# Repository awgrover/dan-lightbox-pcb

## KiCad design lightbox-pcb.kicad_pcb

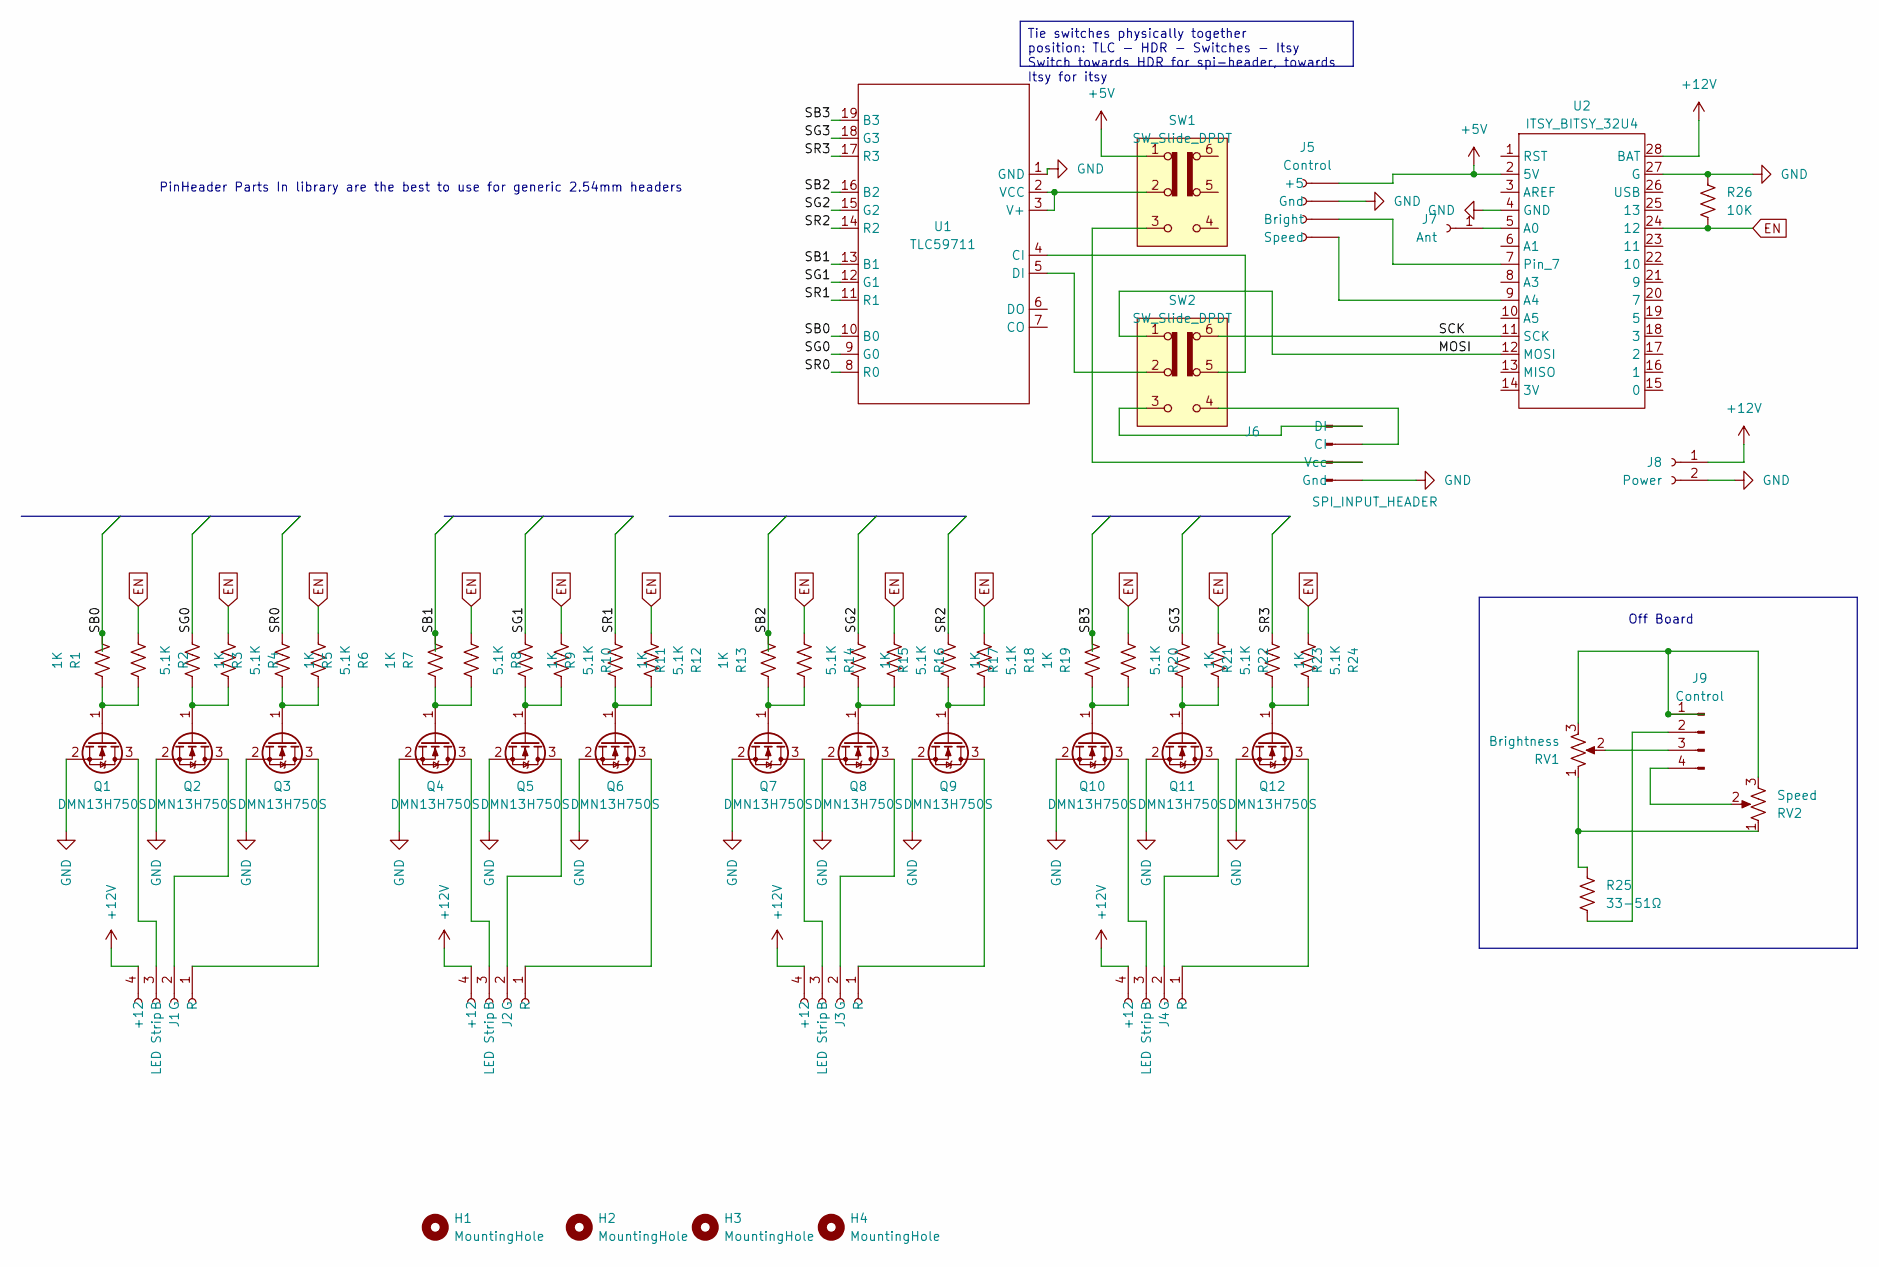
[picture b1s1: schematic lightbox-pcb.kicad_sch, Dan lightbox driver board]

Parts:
H1, H2, H3, H4: MountingHole; MountingHole_4.3mm_M4
J1, J2, J3, J4: LED Strip; PhoenixContact_MC_1,5_4-G-3.5_1x04_P3.50mm_Horizontal
J5: Control; PinHeader_1x04_P2.54mm_Vertical
J6: SPI_INPUT_HEADER; PinHeader_1x04_P2.54mm_Vertical
J7: Ant; PinHeader_1x01_P2.54mm_Vertical
J8: Power; Samtec_HPM-02-01-x-S_Straight_1x02_Pitch5.08mm
J9: Control; PhoenixContact_MSTBVA_2,5_4-G-5,08_1x04_P5.08mm_Vertical
Q1, Q2, Q3, Q4, Q5, Q6, Q7, Q8, Q9, Q10, Q11, Q12: DMN13H750S; SOT-23
R1, R3, R5, R7, R9, R11, R13, R15, R17, R19, R21, R23: 1K; R_0805_2012Metric_Pad1.20x1.40mm_HandSolder
R2, R4, R6, R8, R10, R12, R14, R16, R18, R20, R22, R24: 5.1K; R_0805_2012Metric_Pad1.20x1.40mm_HandSolder
R25: 33-51Ω; Dan_Through_Hole_Res
R26: 10K; R_0805_2012Metric_Pad1.20x1.40mm_HandSolder
RV1: Brightness
RV2: Speed
SW1, SW2: SW_Slide_DPDT; SW_CK_JS202011CQN_DPDT_Straight
U1: TLC59711
U2: ITSY_BITSY_32U4; Itsy_bitsy_32u4

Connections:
+5V: J5.1 (+5), SW1.1 (A), U2.2 (5V)
+12V: J1.4 (+12), J2.4 (+12), J3.4 (+12), J4.4 (+12), J8.1, U2.28 (BAT)
/MOSI: SW2.1 (A), U2.12 (MOSI)
/SB0: R1.2, U1.10 (B0)
/SB1: R7.2, U1.13 (B1)
/SB2: R13.2, U1.16 (B2)
/SB3: R19.2, U1.19 (B3)
/SCK: SW2.6 (C), U2.11 (SCK)
/SG0: R3.2, U1.9 (G0)
/SG1: R9.2, U1.12 (G1)
/SG2: R15.2, U1.15 (G2)
/SG3: R21.2, U1.18 (G3)
/SR0: R5.2, U1.8 (R0)
/SR1: R11.2, U1.11 (R1)
/SR2: R17.2, U1.14 (R2)
/SR3: R23.2, U1.17 (R3)
EN: R2.2, R4.2, R6.2, R8.2, R10.2, R12.2, R14.2, R16.2, R18.2, R20.2, R22.2, R24.2, R26.1, U2.24 (12)
GND: J5.2 (Gnd), J6.4 (Gnd), J8.2, Q1.2 (S), Q2.2 (S), Q3.2 (S), Q4.2 (S), Q5.2 (S), Q6.2 (S), Q7.2 (S), Q8.2 (S), Q9.2 (S), Q10.2 (S), Q11.2 (S), Q12.2 (S), R26.2, U1.1 (GND), U2.4 (GND), U2.27 (G)
unnamed: J1.3 (B), Q1.3 (D)
unnamed: J1.2 (G), Q2.3 (D)
unnamed: J1.1 (R), Q3.3 (D)
unnamed: J2.3 (B), Q4.3 (D)
unnamed: J2.2 (G), Q5.3 (D)
unnamed: J2.1 (R), Q6.3 (D)
unnamed: J3.3 (B), Q7.3 (D)
unnamed: J3.2 (G), Q8.3 (D)
unnamed: J3.1 (R), Q9.3 (D)
unnamed: J4.3 (B), Q10.3 (D)
unnamed: J4.2 (G), Q11.3 (D)
unnamed: J4.1 (R), Q12.3 (D)
unnamed: J5.3 (Bright), U2.7
unnamed: J5.4 (Speed), U2.9 (A4)
unnamed: J6.2 (CI), SW2.4 (A)
unnamed: J6.1 (DI), SW2.3 (C)
unnamed: J6.3 (Vcc), SW1.3 (C)
unnamed: J7.1, U2.5 (A0)
unnamed: J9.1, RV1.3, RV2.3
unnamed: J9.2, R25.1
unnamed: J9.3, RV1.2
unnamed: J9.4, RV2.2
unnamed: Q1.1 (G), R1.1, R2.1
unnamed: Q2.1 (G), R3.1, R4.1
unnamed: Q3.1 (G), R5.1, R6.1
unnamed: Q4.1 (G), R7.1, R8.1
unnamed: Q5.1 (G), R9.1, R10.1
unnamed: Q6.1 (G), R11.1, R12.1
unnamed: Q7.1 (G), R13.1, R14.1
unnamed: Q8.1 (G), R15.1, R16.1
unnamed: Q9.1 (G), R17.1, R18.1
unnamed: Q10.1 (G), R19.1, R20.1
unnamed: Q11.1 (G), R21.1, R22.1
unnamed: Q12.1 (G), R23.1, R24.1
unnamed: R25.2, RV1.1, RV2.1
unnamed: SW2.5 (B), U1.4 (CI)
unnamed: SW2.2 (B), U1.5 (DI)
unnamed: SW1.2 (B), U1.2 (VCC), U1.3 (V+)

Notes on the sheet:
Off Board
PinHeader Parts In library are the best to use for generic 2.54mm headers
Tie switches physically together position: TLC - HDR - Switches - Itsy Switch towards HDR for spi-header, towards Itsy for itsy

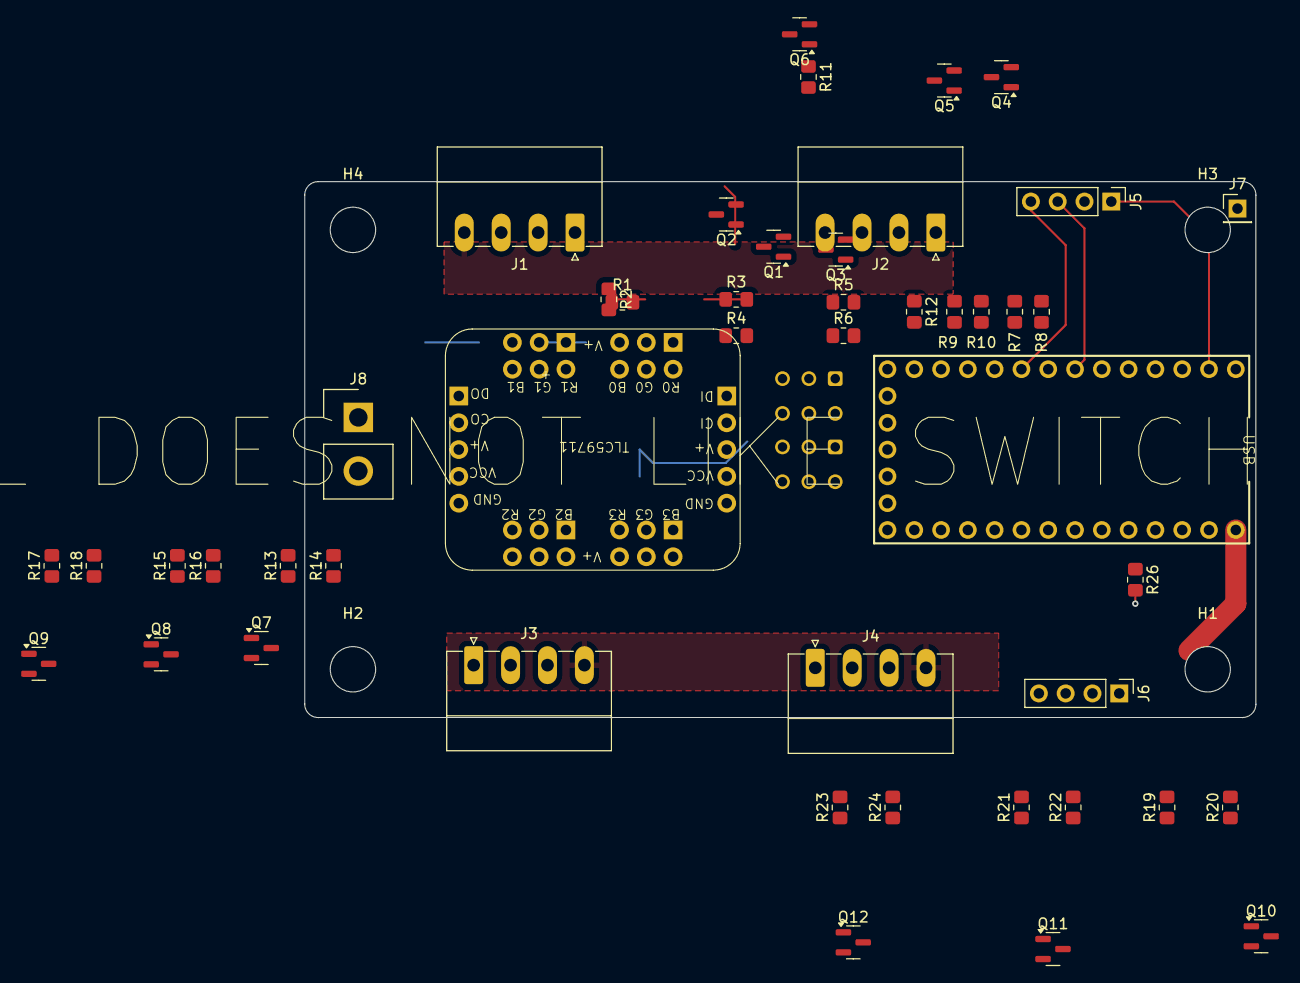
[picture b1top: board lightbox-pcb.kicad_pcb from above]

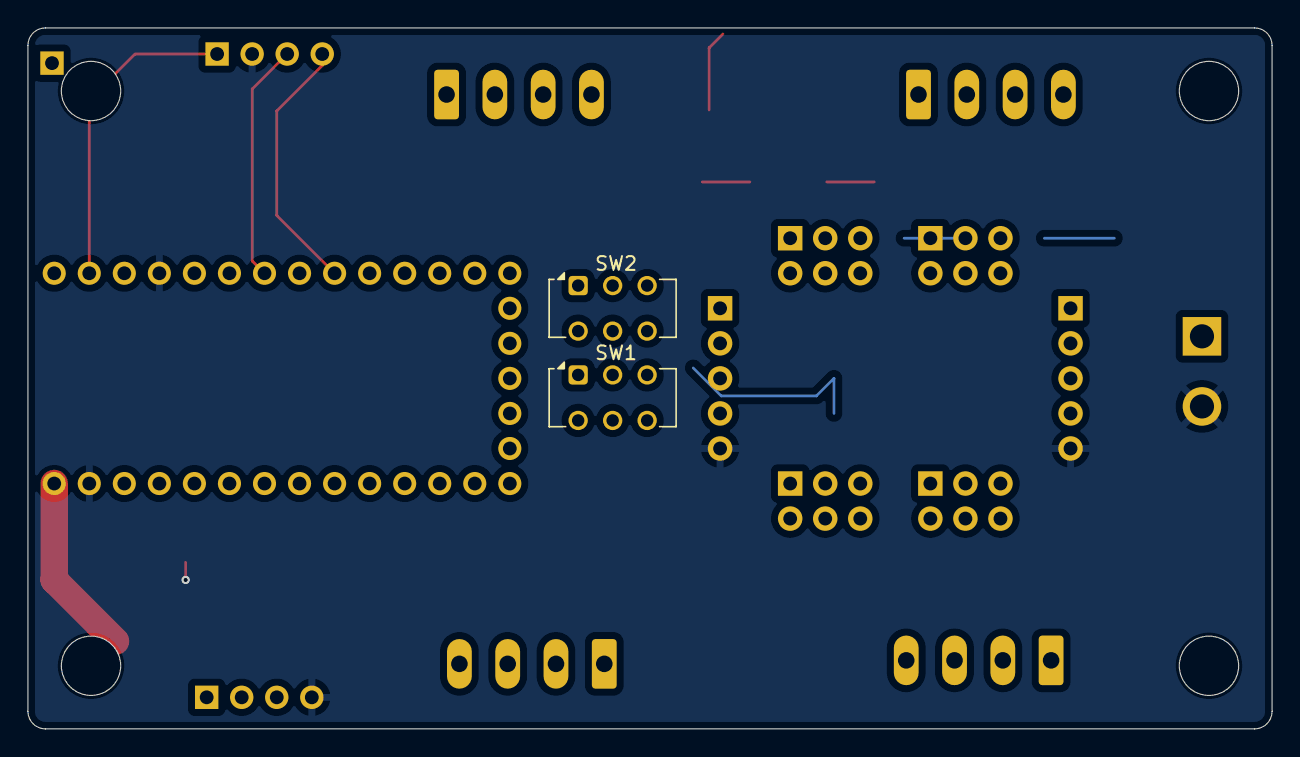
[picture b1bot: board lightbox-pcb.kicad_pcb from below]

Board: 2 copper layers, 90.2 x 50.8 mm, 53 parts (2 on the bottom side), 51 nets.

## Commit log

2025-03-18 early
2025-03-18 wrong files
2025-03-18 WILL DOES NOT LIKE SWITCH
